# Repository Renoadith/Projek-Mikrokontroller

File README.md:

# Rancang Bangun Alat Pendeteksi Kebisingan Berbasis Sensor untuk Analisis Lingkungan Suara

https://github.com/Renoadith/Projek-Mikrokontroller/assets/134272498/ef301c9a-c806-4f26-9cb7-10bee5172634
  
Proyek ini bertujuan mengembangkan alat pendeteksi kebisingan berbasis sensor untuk menganalisis lingkungan suara secara efektif. Menggunakan sensor suara KY-037, alat ini mendeteksi kebisingan dan memberikan peringatan audio ketika kebisingan melebihi ambang batas yang ditentukan. Data dari sensor diolah oleh mikrokontroler Arduino Uno, yang menghasilkan output berupa suara peringatan melalui buzzer. Alat ini cocok untuk lingkungan yang memerlukan ketenangan, seperti perpustakaan, ruang belajar, atau ruang kerja, dan dirancang untuk ditempatkan di setiap sudut ruangan atau kelompok meja agar dapat memantau seluruh area. Proyek ini merupakan bagian dari mata kuliah workshop mikrokontroler yang dikerjakan oleh mahasiswa Teknik Elektronika Politeknik Elektronika Negeri Surabaya (PENS), yang mengaplikasikan pengetahuan praktis dalam mikrokontroler dan sensor untuk menciptakan solusi teknis nyata, menjadikan lingkungan lebih nyaman dan produktif.
  
## Desain 3D

Desain 3D di atas merupakan gambaran akhir alat yang mencakup ukuran, posisi komponen, dan file perangkat lunak untuk pencetakan 3D. Desain ini dibuat menggunakan Fusion 360 karena kemudahan penggunaan dan kemampuan desainer. Fusion 360 memudahkan penentuan posisi komponen dengan presisi tinggi dan menawarkan fitur simulasi serta analisis struktural, memastikan alat sesuai spesifikasi teknis. Perangkat lunak ini juga memungkinkan evaluasi kekuatan dan daya tahan alat sebelum pencetakan, mengurangi risiko kesalahan dan memastikan kualitas. Dengan Fusion 360, desainer dapat mengoptimalkan tata letak komponen sesuai rancangan awal. Pemilihan Fusion 360 didasarkan pada efisiensi dan kemampuan desainer, membuat proses desain lebih cepat dan akurat. Desain akhir diekspor dalam format kompatibel dengan berbagai printer 3D, memastikan pencetakan mudah dan cepat. Penggunaan Fusion 360 memastikan desain 3D alat ini akurat, optimal, dan mendukung kelancaran proses produksi.
  
Link desain 3D (bagian dalam) ==> <a href="Desain/bagian dalam.stl">File desain 3D (bagian dalam)</a>  
Link desain 3D (bagian luar) ==> <a href="Desain/bagian luar.stl">File desain 3D (bagian luar)</a>  
Link video tutorial desain 3D ==> <a href="https://youtu.be/fg9aguebhW4?si=BZ69bgbV-qRVRXbO">Video desain 3D</a>  
Link Thingiverse ==> <a href="https://www.thingiverse.com/thing:6647773">File Thingiverse</a>

---
## List Komponen  

1. Hardware  
   a. Arduino UNO  
   b. Sensor suara KY-037  
   c. Speaker subwoofer   
   d. LCD 16x2 + i2C  
   e. LED 5mm  
   f. GF1002-PAM8403 Stereo Audio Amplifier Module
   
3. Software  
   a. Arduino ide  
   b. HxD
   d. Audacity  
   e. Inventor  
   f. Eagle  
   g. Visual Studio Code (VSC) 
   
5. Alat  
   a. Solder  
   b. Timah solder  
   c. Kabel jumper  
   d. Breadboard  
   e. Obeng  
---
## Blok Diagram  
  
Berikut adalah cara kerja sistem dari alat pendeteksi kebisingan :
1. Menyambungkan sumber listrik berupa adaptor ke arduino uno agar dapat dioperasikan
2. Kemudianmenggunakan input berupa sensor Ky-037 (untuk menangkap suara)
3. Arduino uno sebagai mikrokontroler dengan penggunaan software visual studio code untuk menyesuaikan program (batas maksimal suara yang ditangkap)
4. Suara yang ditangkap oleh sensor suara (Ky-037) akan diteruskan dan diproses oleh arduino uno. Jika melewati batas maksimal dari program, output speaker, LED, dan LCD akan bekerja
5. Speaker akan menghasilkan suara bertujuan untuk mengingatkan agar mengurangi kebisingan suara
6. LED akan menyala sebagai indikator bahwa sedang terjadi kebisingan
7. modul I2C akan memroses suara yang sudah ditangkap oleh sensor Ky-037, kemudian menampilkan besarnya nilai dari suara pada LCD

---
## Rangkaian Simulasi  

Simulasi adalah tahap penting dalam uji coba sistem untuk memastikan semua komponen berfungsi baik sebelum implementasi nyata. Untuk proyek alat pendeteksi kebisingan ini, kami menggunakan platform web Tinkercad karena kemudahannya diakses dan gratis, memungkinkan kalian mencoba simulasi tanpa biaya. Kami menggunakan rangkaian garis besar, dengan tombol tekan sebagai input untuk menggantikan sensor suara yang tidak tersedia di simulator. Output berupa buzzer sebagai indikator suara dan LCD untuk menandakan status aktif atau tidaknya rangkaian. Tinkercad memudahkan pembuatan dan pengujian desain rangkaian secara efektif, meskipun tidak memiliki semua komponen yang diinginkan. Platform ini menyediakan alat simulasi memadai untuk memvisualisasikan fungsi rangkaian dalam kondisi nyata, membantu mengidentifikasi dan memperbaiki masalah sebelum produksi fisik. Dengan Tinkercad, kami menghemat waktu dan biaya sambil memastikan desain sesuai spesifikasi.  
  
Link web simulasi ==> <a href="https://www.tinkercad.com/things/jV3vWOUGUW2-simulasi/editel">Simulasi software</a>  
Link video simulasi ==> <a href="https://youtu.be/cqOJ23cZhoI?si=dtuSKsLPAU53A1Sa">Video simulasi software</a>  

---
## Rangkaian Skematik

Perangkaian skematik pada proyek ini adalah tahap desain untuk mencetak PCB, dibuat menggunakan perangkat lunak Eagle. Pemilihan Eagle didasarkan pada kemudahan penggunaan dan keahlian desainer, serta kebiasaan penggunaan dalam perkuliahan. Eagle memungkinkan perancangan skematik dengan presisi tinggi dan memudahkan proses routing jalur PCB. Dengan antarmuka intuitif dan berbagai alat bantu desain, perangkat lunak ini memastikan semua komponen terhubung dengan benar dan layout PCB dioptimalkan untuk kinerja terbaik. Desain skematik yang dihasilkan kemudian diekspor untuk pencetakan PCB, memastikan semua jalur dan koneksi sesuai spesifikasi. Dengan Eagle, kami dapat menghasilkan desain yang efisien, akurat, dan siap untuk tahap produksi.
  
Link skematik ==> <a href="https://github.com/Renoadith/Projek-Mikrokontroller/blob/main/Schematik/Alat%20pendeteksi%20kebisingan.sch">File skematik</a>  
Link board ==> <a href="https://github.com/Renoadith/Projek-Mikrokontroller/blob/main/Schematik/Alat%20pendeteksi%20kebisingan.brd">File board</a>  
Link video tutorial skematik ==> <a href="https://youtu.be/qFakJmJQMaU?feature=shared">Video skematik</a>  

---
## Sistem Audio dan Program

Perangkaian skematik pada proyek ini dirancang untuk mencetak PCB menggunakan perangkat lunak Eagle. Eagle dipilih karena kemudahan penggunaan dan keahlian desainer dalam perangkat lunak ini. Perangkat lunak ini memungkinkan perancangan skematik dengan presisi tinggi dan memudahkan routing jalur PCB. Desain yang dihasilkan memastikan semua komponen terhubung dengan benar dan layout PCB dioptimalkan. Hasil desain kemudian diekspor untuk pencetakan PCB, memastikan jalur dan koneksi sesuai spesifikasi. Dengan Eagle, desain yang efisien dan akurat siap untuk tahap produksi.
  
Link audio (Audacity) ==> <a href="https://github.com/Renoadith/Projek-Mikrokontroller/blob/main/Program/AUDIO%20rekam">File audio</a>  
Link audio (HxD) ==> <a href="https://github.com/Renoadith/Projek-Mikrokontroller/blob/main/Program/AUDIO%20rekam.raw">File audio</a>  
Link video tutorial audio ==> <a href="https://youtu.be/W0XZ7WrG6vU">Video audio</a>  

---
## Proses Pengerjaan  
Berikut adalah prosesdur pengerjaan dari proyek alat pendeteksi kebisingan :  
#### 1.  Simulasi Perangkat Lunak:  
Melakukan simulasi rangkaian menggunakan Tinkercad untuk memastikan semua komponen berfungsi dengan baik sebelum implementasi nyata.  

#### 2. Pembuatan Desain 3D:  
Menggunakan Fusion 360 untuk membuat desain 3D alat, mencakup ukuran, posisi komponen, dan file perangkat lunak untuk pencetakan 3D.  

#### 3. Perancangan Skematik PCB:  
Membuat desain skematik PCB menggunakan perangkat lunak Eagle, memastikan semua komponen terhubung dengan benar dan jalur dioptimalkan.  

#### 4. Pencetakan PCB:  
Mengekspor desain skematik untuk pencetakan PCB, memastikan semua jalur dan koneksi sesuai dengan spesifikasi.  

#### 5. Pengumpulan Semua Komponen:  
Mengumpulkan semua komponen elektronik yang diperlukan berdasarkan desain skematik yang telah dibuat.  

#### 6. Soldering Komponen:  
Melakukan penyolderan komponen pada PCB yang telah dicetak sesuai dengan desain skematik.  

#### 7. Rekaman dan Pengeditan Audio:  
Merekam dan mengedit audio menggunakan Audacity dan HxD untuk membuat peringatan berbasis audio yang akan digunakan oleh alat.  

#### 8.Uji Coba Alat:  
Menguji alat secara menyeluruh untuk memastikan semua komponen bekerja sesuai rencana dan alat berfungsi dengan baik dalam mendeteksi kebisingan.  

#### 9. Evaluasi dan Finishing:  
Mengevaluasi kinerja alat, melakukan penyesuaian dan perbaikan jika diperlukan, dan menyelesaikan tahap akhir pengembangan alat.  

#### 10. Demonstrasi Alat:  
Melakukan demonstrasi alat kepada pihak terkait, menunjukkan fungsionalitas dan efektivitas alat pendeteksi kebisingan.  

**Dengan mengikuti prosedur ini, proyek dapat diselesaikan secara sistematis dan efisien, memastikan setiap tahap dilakukan dengan cermat dan hasil akhirnya berkualitas tinggi.**

---

## Dokumentasi

#### MEKANIK

#### PERAKITAN

#### PROGRAM

#### DEMO VIDEO IKLAN 
https://github.com/Renoadith/Projek-Mikrokontroller/assets/168974067/a5bf39f3-afec-4e52-a946-437841fa6f4a  

Link lebih jelas ==> <a href="https://youtu.be/7oVi07qgA7E?si=QuQN2IhZiEXbEfBq">Video iklan</a>

---

## Flayer

Link penjelasan lebih lengkap ==> <a href="https://youtu.be/Oe4GmpdsbrU">Video presentasi</a>

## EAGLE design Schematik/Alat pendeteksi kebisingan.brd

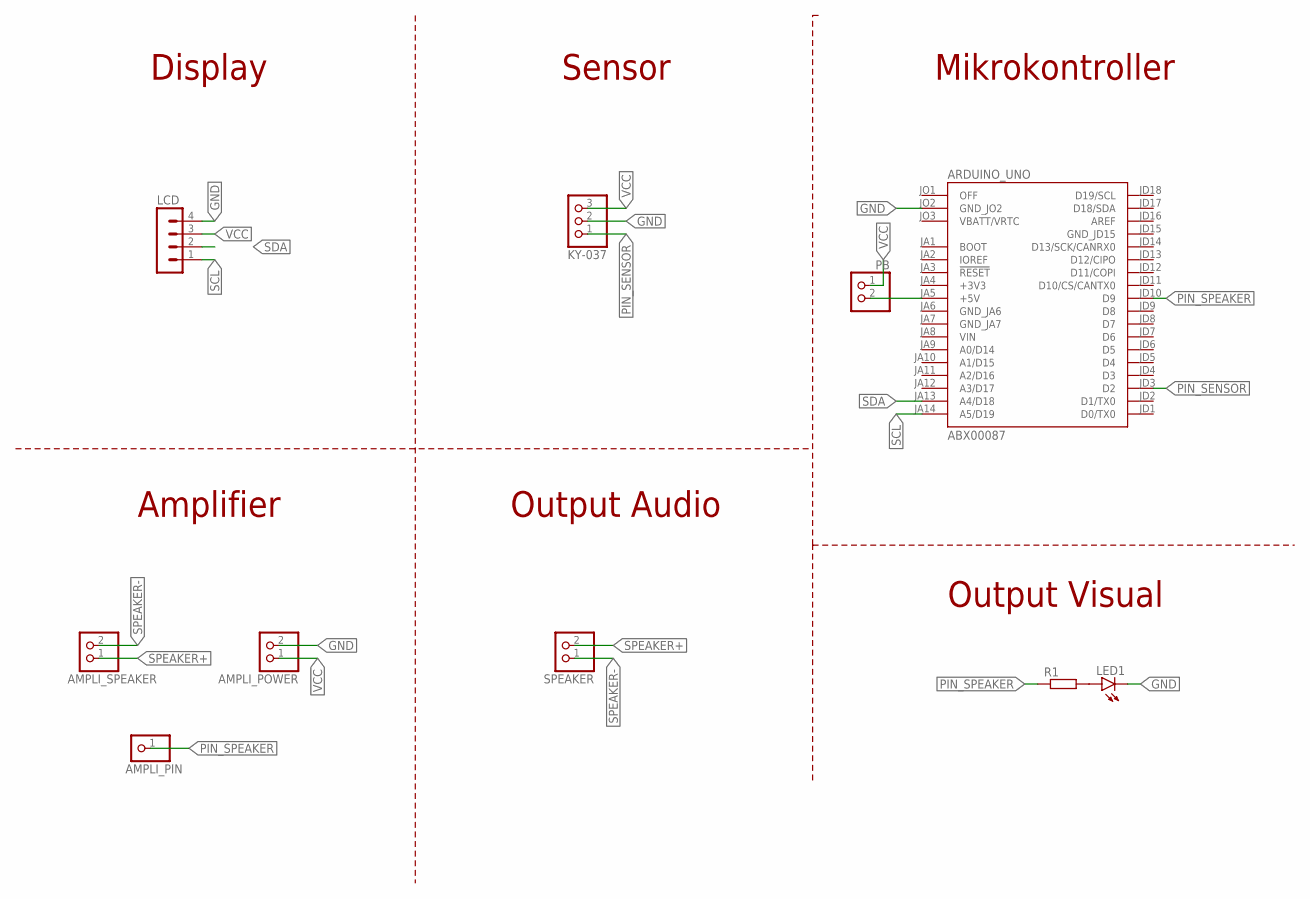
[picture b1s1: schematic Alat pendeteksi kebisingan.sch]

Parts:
AMPLI_PIN: PINHD-1X1; 1X01
AMPLI_POWER: PINHD-1X2; 1X02
AMPLI_SPEAKER: PINHD-1X2; 1X02
ARDUINO_UNO: ABX00087; MODULE_ABX00087
KY-037: PINHD-1X3; 1X03
LCD: MA04-1
LED1: LED3MM
PB: PINHD-1X2; 1X02
R1: R-EU_0207/10; 0207/10
SPEAKER: PINHD-1X2; 1X02

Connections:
+3V3: ARDUINO_UNO.JA4 (+3V3)
GND: AMPLI_POWER.2, ARDUINO_UNO.JO2 (GND_JO2), KY-037.2, LCD.4, LED1.K (C)
GND_JA6: ARDUINO_UNO.JA6 (GND_JA6)
GND_JA7: ARDUINO_UNO.JA7 (GND_JA7)
GND_JD15: ARDUINO_UNO.JD15 (GND_JD15)
unnamed: ARDUINO_UNO.JA5 (+5V), PB.2
unnamed: LED1.A, R1.2
P: ARDUINO_UNO.JA8 (VIN)
PIN_SENSOR: ARDUINO_UNO.JD3 (D2), KY-037.1
PIN_SPEAKER: AMPLI_PIN.1, ARDUINO_UNO.JD10 (D9), R1.1
SCL: ARDUINO_UNO.JA14 (A5/D19), LCD.1
SDA: ARDUINO_UNO.JA13 (A4/D18), LCD.2
SPEAKER+: AMPLI_SPEAKER.1, SPEAKER.2
SPEAKER-: AMPLI_SPEAKER.2, SPEAKER.1
VBATT/VRTC: ARDUINO_UNO.JO3 (VBATT/VRTC)
VCC: AMPLI_POWER.1, KY-037.3, LCD.3, PB.1

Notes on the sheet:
Mikrokontroller
Sensor
Display
Amplifier
Output Audio
Output Visual

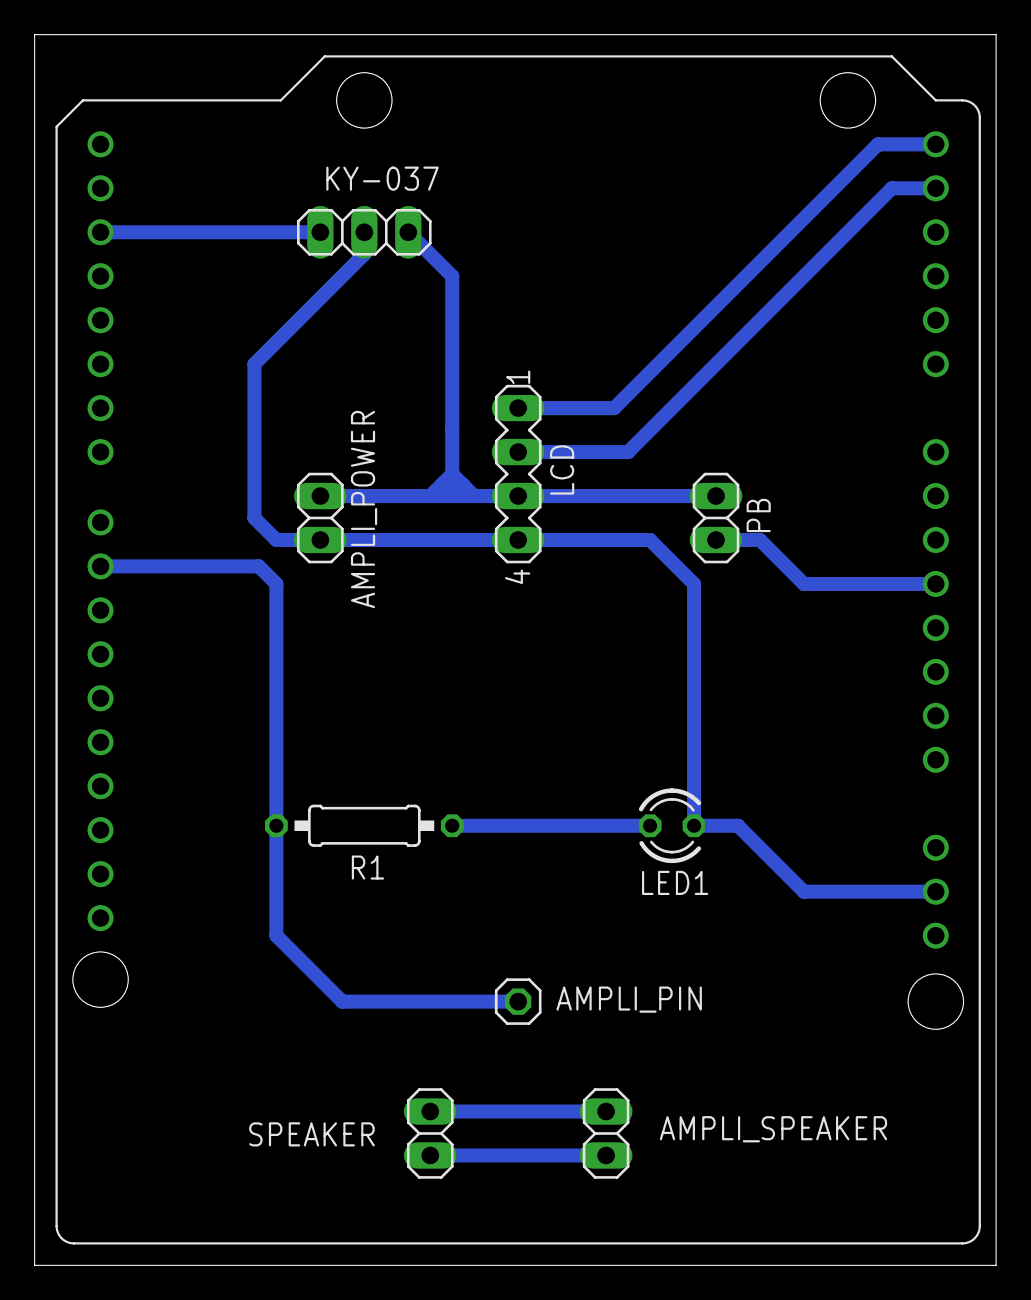
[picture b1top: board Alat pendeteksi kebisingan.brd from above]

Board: 2 copper layers, 55.5 x 71.1 mm, 10 parts (0 on the bottom side), 10 nets.

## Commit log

2024-05-05 Rename README.md to Informasi.md
2024-05-05 Rename Informasi.md to README.md
2024-05-07 Create Proposal
2024-05-07 Create progres 1
2024-05-07 Create Desain
2024-05-07 Create Daftar Pustaka
2024-05-07 Update Daftar Pustaka
2024-05-14 Update progres 1
2024-05-14 Create Flow Chart
2024-05-19 Create List komponen
2024-05-19 Create Link youtube
2024-05-21 Create Schematic
2024-05-21 Create p
2024-05-21 Create konvert audio to hex
2024-05-27 Update and rename progres 1 to Tanpa LCD (main.pp)
2024-05-27 Audio to hex (Audio.h)
2024-05-27 Create Tanpa LCD (main.pp)
2024-05-27 Create Audio to Hex (Berisik.h)
2024-05-27 Create Cara Memasukkan Audio pada program
2024-05-27 Update List komponen
2024-05-27 README.md
2024-05-28 Rename IMG_20240528_112058.jpg to Rangkaian Simulasi
2024-06-03 Komponen/IMG20240524234516.jpg
